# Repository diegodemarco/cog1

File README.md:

# cog1

## What is cog1?
cog1 is an open-source industrial IoT gateway (hardware and software) built as a motherboard hosting an [Orange Pi Zero 3](http://www.orangepi.org/html/hardWare/computerAndMicrocontrollers/details/Orange-Pi-Zero-3.html) linux SBC (Wiki [here](http://www.orangepi.org/orangepiwiki/index.php/Orange_Pi_Zero_3)).
- The motherboard was designed using [KiCad](https://www.kicad.org/).
- Its software uses the [.net core framework](https://dotnet.microsoft.com/) (currently at version 8) to provide the services running in the hardware, as well as the back-end web services for the UI.
- It also hosts the user interface (console), which is written  in [Angular](https://angular.dev/), based on the [Core-UI admin template](https://coreui.io/product/free-angular-admin-template/).
- In essence, it's a fully self-contained IoT gateway capable of interfacing with sensors and actuators directly, designed to process data, make local decisions, and communicate with external cloud services if needed.

### Features

#### Hardware
The cog1 platform currently supports:
- Powered by any DC supply from 12 to 24 VDC.
- Four digital inputs (isolated, using two [ISO 1212](https://www.ti.com/lit/ds/symlink/iso1212.pdf) chips from TI).
- Four digital outputs (relays, varistor-protected).
- Four analog voltage inputs (0-10 V, non-isolated), protected up to 48 VDC. The ADC is an [ADC128D818](https://www.ti.com/lit/ds/symlink/adc128d818.pdf) chip from TI.
- Four analog current inputs (0-20 mA, non isolated), protected up to 100 mA. Uses the same [ADC128D818](https://www.ti.com/lit/ds/symlink/adc128d818.pdf) chip as the voltage inputs.
- One RS-485 port (tested from 9600 to 115200 bauds). Support for Modbus RTU is already built on top of this.
- Battery-backed RTC.
- A simple but extensible user interface with a small OLED display and a rotary encoder + pushbutton.
- All connectivity inherited from the Orange Pi Zero 3 SBC
  - 1 Gb Ethernet
  - 2.4 + 5.8 GHz WiFi
  - Bluetooth 5
  - A front USB port (USB 2.0)

#### Software

The current software is rather basic, but includes everything needed to fully test the hardware. Additionally, the software already has the correct "architecture", i.e. it is designed as a linux service file that can be started, stopped, etc., and communicates with the hardware through a low-level i/o library created with native code (plain old C).

The front-end (console) is written in Angular, based on the [Core-UI admin template](https://coreui.io/product/free-angular-admin-template/), and it communicates with the back-end via web-services, which are already integrated in such a way that creating new controllers/endpoints and consuming them from the front-end is really simple. 

The following features are already implemented:
- Internal variables are fully supported. These match the actual hardware of the cog1.
- External variables can be defined as well, based on Modbus registers.
- Both Modbus RTU and Modbus TCP are supported, allowing reading and writing the most common types of registers in a variety of data types.
- Variables can be defined to be "polled" automatically. For variables bound to Modbus registers, this means that the respective registers are polled via RTU or TCP as needed.
- Writeable variables can be controlled/modified from the dashboard.
- Writeable variables bound to Modbus registers also trigger the respective write operations through RTU or TCP, which can be done from the dashboard.

The plan is to continue developing the software so that it can:
- Provide data-extraction web services.
- Communicate with external cloud services via MQTT or any other protocol that could be relevant.
- Allow running javascript code using [Jint](https://github.com/sebastienros/jint) to make it possible to compute complex variables, do edge data-processing, etc.
- Update the console UI to allow further management of all avaible functionality, as it grows over time.

### Hardware
#### PCB

The PCB has been designed using KiCad. It contains everything needed, including a 3D render. All components can be hand-soldered, but a few (essentially the AOZ regulator, the ADC, and the digital input isolators) require a bit of skills, as they are SSOP components. 

All capacitors, resistors, etc. are 0805 or bigger, so they can be hand-soldered with little effort. The PCB contains all necessary headers to allow the Orange Pi Zero 3 to be plugged in, inverted.

All components can be found in the usual marketplaces (DigiKey, Mouser, etc.). I strongly advice not using unreliable (i.e. unrealistically cheap) sources for the components, especially the chips, as there is a large market of fake chips that either don't work, or even worse, work erratically.

#### Enclosure
The enclosure for the cog1 is a rather standard extruded-aluminum case, which can be found online for a few bucks. However, as a 3D printing enthusiast, I ended up designing and printing everything necessary to complete the enclosure:
- Front cover
- Back cover
- Knob

All designs, done in SolidWorks, are included in this project. I have printed everything with an Elegoo Mars 3 Pro (resin), and expect that all parts would print well on any resin 3D printer. I have not tried to print this on a filament printer, as I believe the quality would not be good enough. When printed in resin, all parts really look production-grade if the proper resin is used.

### Software
#### Main back-end code
The main code of the cog1 platform is a .net core application that contains all the necessary components (web services and general logic) to keep the cog1 working. The current version is relatively basic, and only contains those features needed to test the hardware. A web service is in place to provide basic status of the cog1, which is currently used to test the overall reliability of the hardware. All hardware functions have been tested with this software.

This is by far the area that needs the most effort, so that the cog1 can be turned into a fully-functional gateway.

#### Native back-end code
There are a few small portions of the software written in plan old C, and compiled directly in the SBC:
- A low-level i/o library that deals with digital and analog i/o, display, etc.
- A small "logo" application (configured as a service that starts early in the Linux boot process) to display the cog1 logo while the cog1 is booting.

Everything else is c#, so there's no low-level really in the c# code. 

#### Front-end code
The front-end (console) is written in Angular, based on the [Core-UI admin template](https://coreui.io/product/free-angular-admin-template/), and it communicates with the back-end via web-services, which are already integrated in such a way that creating new controllers/endpoints and consuming them from the front-end is really simple. While the functionality is relatively limited at the moment, the front-end contains all the necessary building-blocks to be extended easily:
- It communicates with the back-end via web-services, with proxies created using [swagger-typescript-api](https://github.com/acacode/swagger-typescript-api). This makes it very simple to create new controllers and endpoints in the back-end andthen use them in the front-end with full type-checking and code insight.
- It handles authentication with the back-end.
- It fully supports loading literals (in the language of the user) from the back-end, before the application starts.

## Getting started
### Building the hardware
The KiCad project included in the pcb folder contains everything needed to manufacture the pcb. For all prototypes, the pcb was ordered to PCBWay, and then all components were soldered manually. When soldering, I strongly advise mounting the switching power supply first, veryfying the 5V are steady and noiseless, and then mount everything else. This is to prevent blowing up anything if the switching power supply was not mounted correctly.

### Installing the software
I'll write a tutorial for this ASAP, but it's pretty straightforward.

## Current status
### What's done
### What's missing

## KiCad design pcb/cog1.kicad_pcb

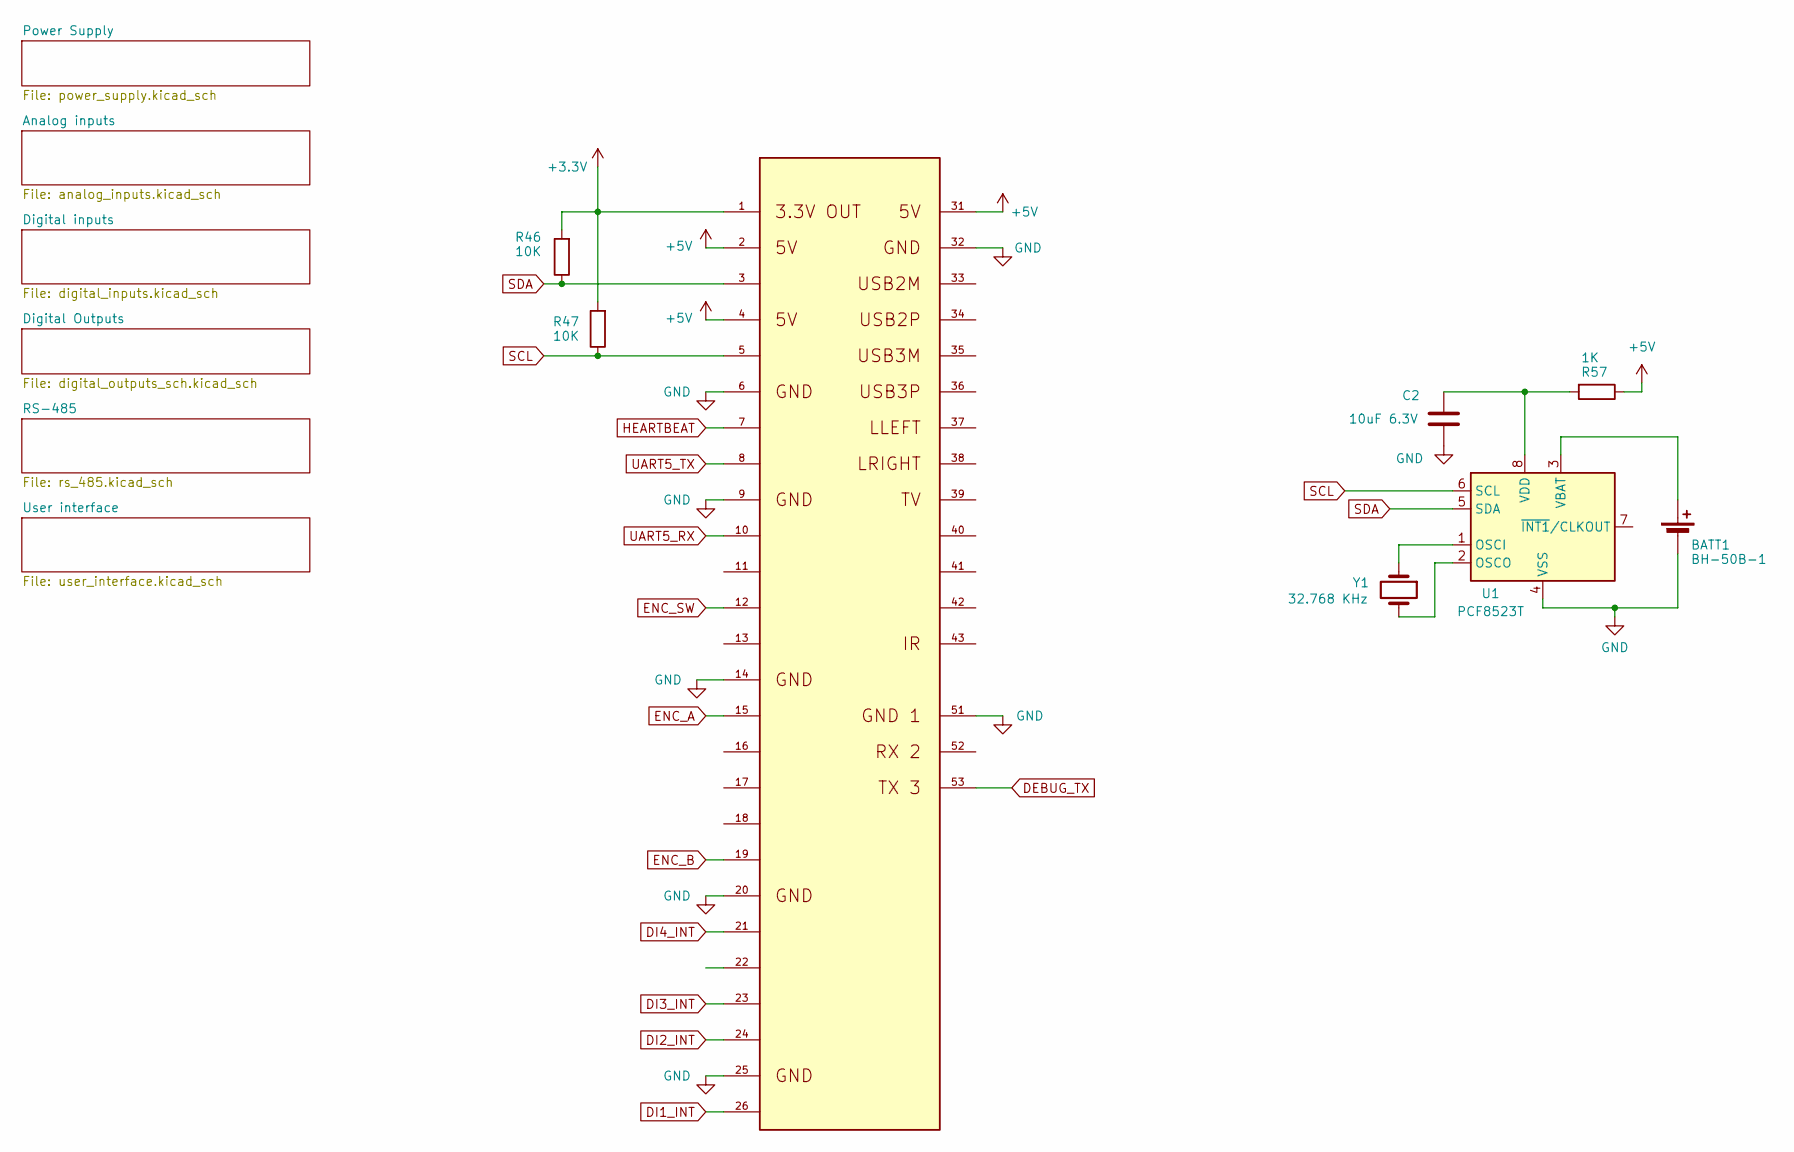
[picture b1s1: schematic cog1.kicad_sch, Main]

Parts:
BATT1: BH-50B-1
C2: 10uF 6.3V; C_0805_2012Metric
R46, R47: 10K; R_0805_2012Metric
R57: 1K; R_0805_2012Metric
U1: PCF8523T; SOIC-8_3.9x4.9mm_P1.27mm
U$1: OPI-ZERO-3
Y1: 32.768 KHz; Crystal_C26-LF_D2.1mm_L6.5mm_Vertical

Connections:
+3.3V: R46.2, R47.2, U$1.1; also elsewhere on the board
+5V: R57.1, U$1.2, U$1.4, U$1.31; also elsewhere on the board
DEBUG_TX: U$1.53; also elsewhere on the board
DI1_INT: U$1.26; also elsewhere on the board
DI2_INT: U$1.24; also elsewhere on the board
DI3_INT: U$1.23; also elsewhere on the board
DI4_INT: U$1.21; also elsewhere on the board
ENC_A: U$1.15; also elsewhere on the board
ENC_B: U$1.19; also elsewhere on the board
ENC_SW: U$1.12; also elsewhere on the board
GND: BATT1.2 (-), C2.1, U1.4 (VSS), U$1.6, U$1.9, U$1.14, U$1.20, U$1.25, U$1.32, U$1.51; also elsewhere on the board
HEARTBEAT: U$1.7; also elsewhere on the board
unnamed: BATT1.1 (+), U1.3 (VBAT)
unnamed: U1.1 (OSCI), Y1.1
unnamed: U1.2 (OSCO), Y1.2
unnamed: C2.2, R57.2, U1.8 (VDD)
SCL: R47.1, U1.6 (SCL), U$1.5; also elsewhere on the board
SDA: R46.1, U1.5 (SDA), U$1.3; also elsewhere on the board
UART5_RX: U$1.10; also elsewhere on the board
UART5_TX: U$1.8; also elsewhere on the board

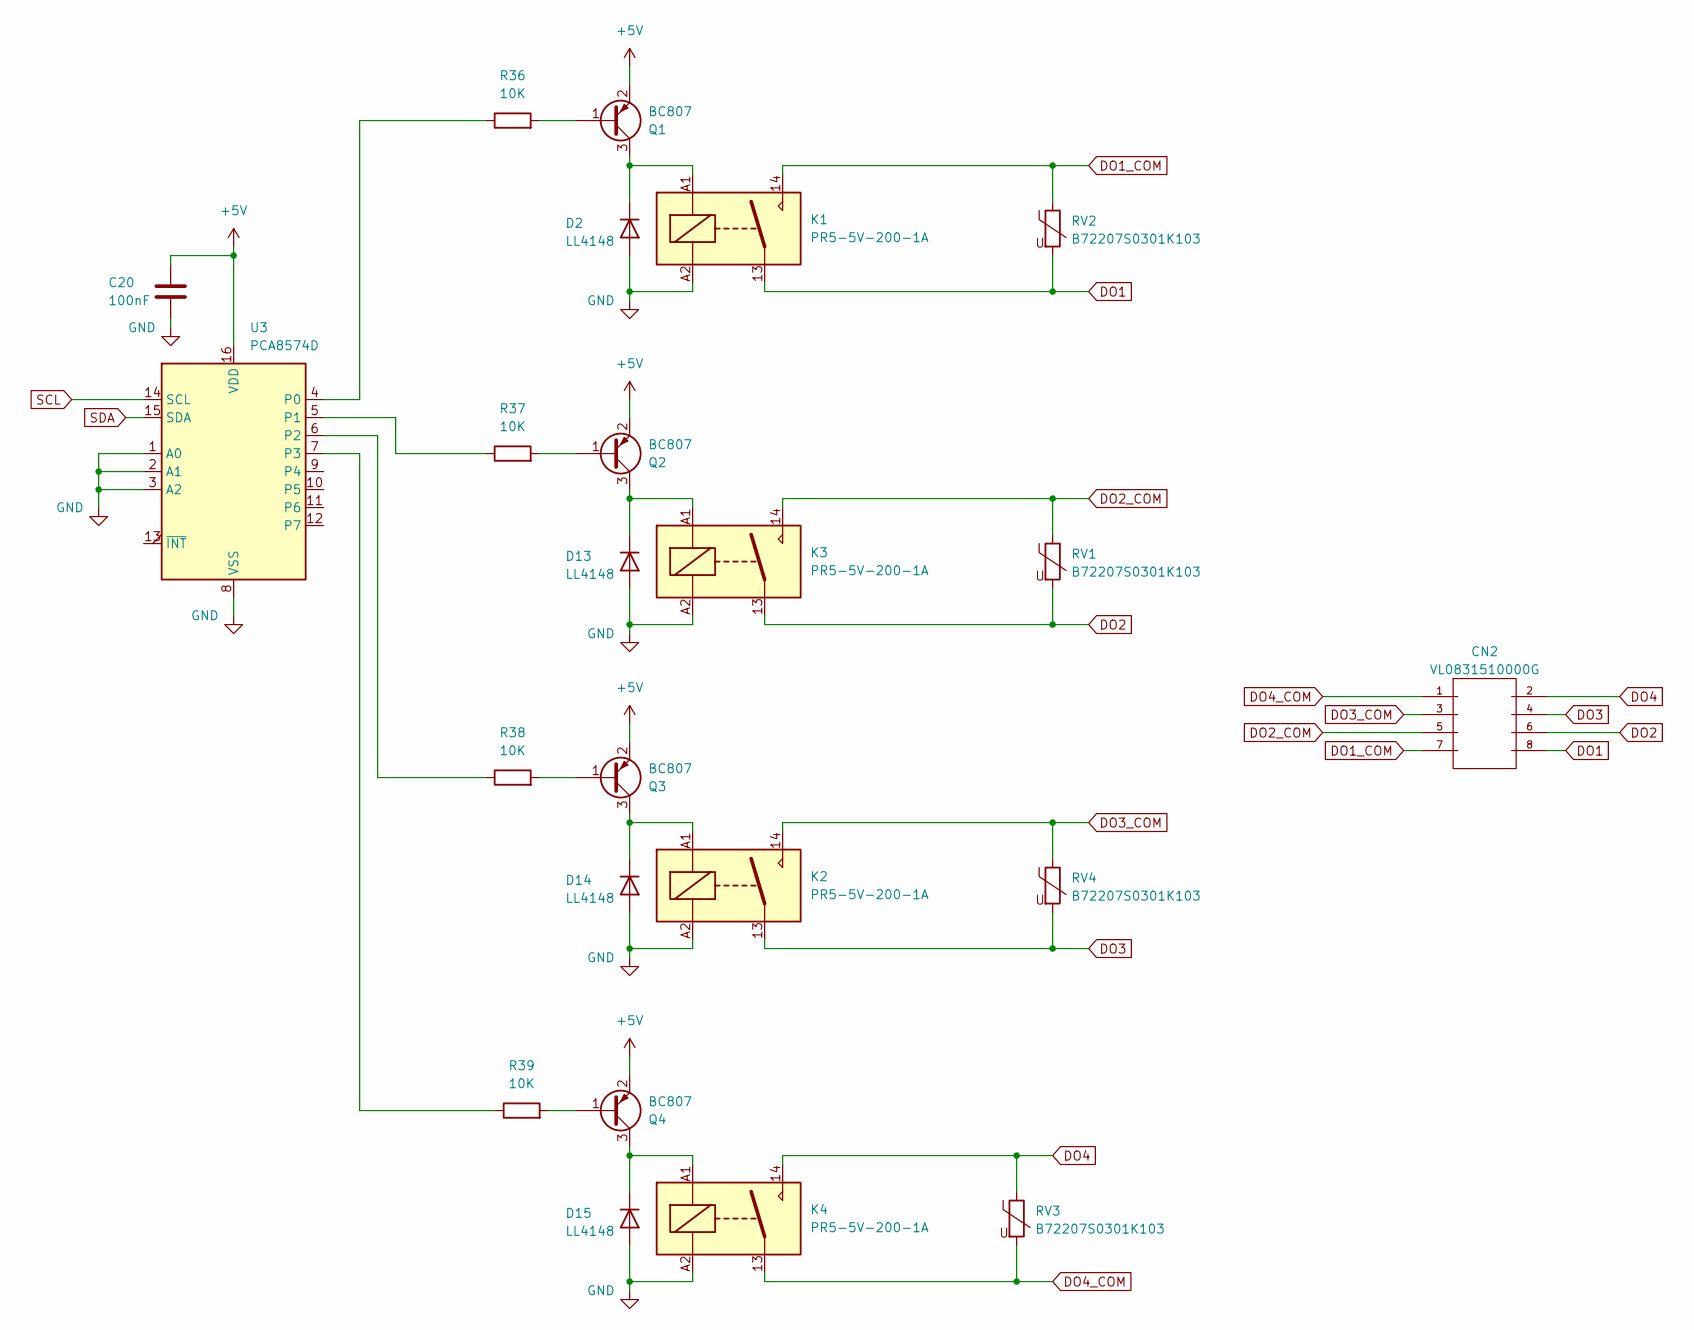
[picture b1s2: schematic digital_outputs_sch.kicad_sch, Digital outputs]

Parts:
C20: 100nF; C_0805_2012Metric
CN2: VL0831510000G
D2, D13, D14, D15: LL4148; D_MiniMELF
K1, K2, K3, K4: PR5-5V-200-1A
Q1, Q2, Q3, Q4: BC807; SOT-23
R36, R37, R38, R39: 10K; R_0805_2012Metric
RV1, RV2, RV3, RV4: B72207S0301K103; RV_Disc_D7mm_W4.5mm_P5mm
U3: PCA8574D; SOIC-16W_7.5x10.3mm_P1.27mm

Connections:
+5V: C20.1, Q1.2 (E), Q2.2 (E), Q3.2 (E), Q4.2 (E), U3.16 (VDD); also elsewhere on the board
DO1: CN2.8, K1.13, RV2.2
DO1_COM: CN2.7, K1.14, RV2.1
DO2: CN2.6, K3.13, RV1.2
DO2_COM: CN2.5, K3.14, RV1.1
DO3: CN2.4, K2.13, RV4.2
DO3_COM: CN2.3, K2.14, RV4.1
DO4: CN2.2, K4.14, RV3.1
DO4_COM: CN2.1, K4.13, RV3.2
GND: C20.2, D2.2 (A), D13.2 (A), D14.2 (A), D15.2 (A), K1.A2, K2.A2, K3.A2, K4.A2, U3.1 (A0), U3.2 (A1), U3.3 (A2), U3.8 (VSS); also elsewhere on the board
unnamed: D2.1 (K), K1.A1, Q1.3 (C)
unnamed: D13.1 (K), K3.A1, Q2.3 (C)
unnamed: D14.1 (K), K2.A1, Q3.3 (C)
unnamed: D15.1 (K), K4.A1, Q4.3 (C)
unnamed: Q1.1 (B), R36.2
unnamed: Q2.1 (B), R37.2
unnamed: Q3.1 (B), R38.2
unnamed: Q4.1 (B), R39.2
unnamed: R36.1, U3.4 (P0)
unnamed: R37.1, U3.5 (P1)
unnamed: R38.1, U3.6 (P2)
unnamed: R39.1, U3.7 (P3)
SCL: U3.14 (SCL); also elsewhere on the board
SDA: U3.15 (SDA); also elsewhere on the board

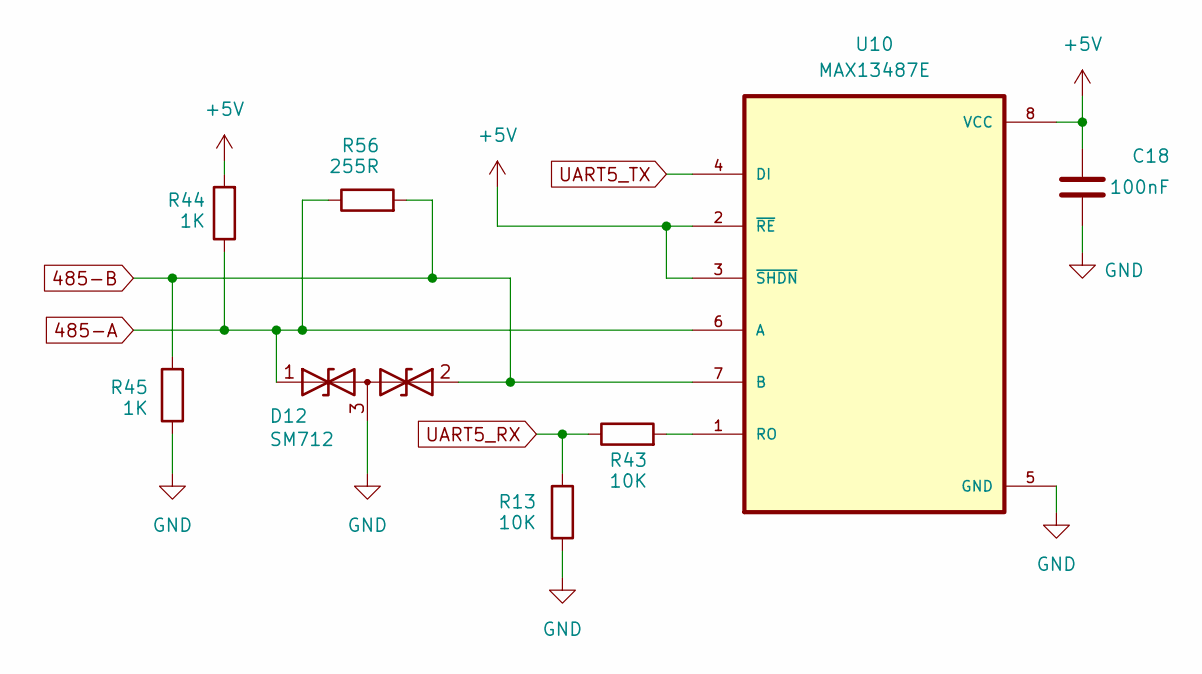
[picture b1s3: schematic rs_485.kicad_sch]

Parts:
C18: 100nF; C_0805_2012Metric
D12: SM712; SOT-23-3
R13, R43: 10K; R_0805_2012Metric
R44, R45: 1K; R_0805_2012Metric
R56: 255R; R_0805_2012Metric
U10: MAX13487E; SOIC-8_3.9x4.9mm_P1.27mm

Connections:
485-A: D12.1 (A1), R44.1, R56.1, U10.6 (A); also elsewhere on the board
485-B: D12.2 (A2), R45.2, R56.2, U10.7 (B); also elsewhere on the board
+5V: C18.2, R44.2, U10.2 (~RE), U10.3 (~SHDN), U10.8 (VCC); also elsewhere on the board
GND: C18.1, D12.3 (common), R13.2, R45.1, U10.5 (GND); also elsewhere on the board
unnamed: R43.2, U10.1 (RO)
UART5_RX: R13.1, R43.1; also elsewhere on the board
UART5_TX: U10.4 (DI); also elsewhere on the board

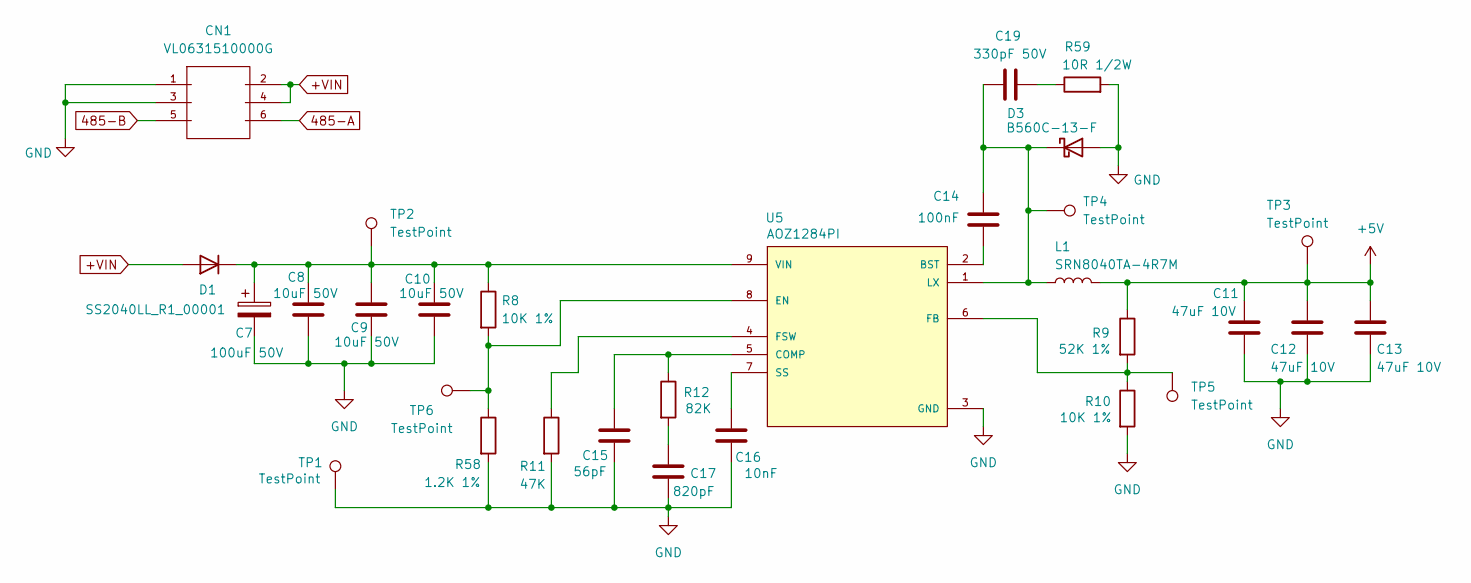
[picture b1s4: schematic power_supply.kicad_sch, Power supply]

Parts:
C7: 100uF 50V; CP_Elec_10x12.6
C8, C9, C10: 10uF 50V; C_1206_3216Metric_Pad1.33x1.80mm_HandSolder
C11, C12, C13: 47uF 10V; C_1206_3216Metric_Pad1.33x1.80mm_HandSolder
C14: 100nF; C_0805_2012Metric
C15: 56pF; C_0805_2012Metric
C16: 10nF; C_0805_2012Metric
C17: 820pF; C_0805_2012Metric
C19: 330pF 50V; C_0805_2012Metric
CN1: VL0631510000G
D1: SS2040LL_R1_00001; D_SOD-123F
D3: B560C-13-F; D_SMC
L1: SRN8040TA-4R7M; Bourns_SRN8040TA
R8, R10: 10K 1%; R_0805_2012Metric
R9: 52K 1%; R_0805_2012Metric
R11: 47K; R_0805_2012Metric
R12: 82K; R_0805_2012Metric
R58: 1.2K 1%; R_0805_2012Metric
R59: 10R 1/2W; R_1206_3216Metric_Pad1.30x1.75mm_HandSolder
TP1, TP2, TP3, TP4, TP5, TP6: TestPoint; TestPoint_Pad_D1.0mm
U5: AOZ1284PI

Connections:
485-A: CN1.6; also elsewhere on the board
485-B: CN1.5; also elsewhere on the board
+5V: C11.1, C12.1, C13.1, L1.2, R9.1, TP3.1; also elsewhere on the board
+VIN: CN1.2, CN1.4, D1.2 (A)
GND: C7.2, C8.2, C9.2, C10.2, C11.2, C12.2, C13.2, C15.1, C16.1, C17.1, CN1.1, CN1.3, D3.2 (A), R10.2, R11.2, R58.2, R59.2, TP1.1, U5.3 (GND); also elsewhere on the board
unnamed: C17.2, R12.2
unnamed: C19.1, R59.1
unnamed: C7.1, C8.1, C9.1, C10.1, D1.1 (K), R8.1, TP2.1, U5.9 (VIN)
unnamed: C14.2, C19.2, D3.1 (K), L1.1, TP4.1, U5.1 (LX)
unnamed: C14.1, U5.2 (BST)
unnamed: C15.2, R12.1, U5.5 (COMP)
unnamed: R8.2, R58.1, TP6.1, U5.8 (EN)
unnamed: R9.2, R10.1, TP5.1, U5.6 (FB)
unnamed: R11.1, U5.4 (FSW)
unnamed: C16.2, U5.7 (SS)

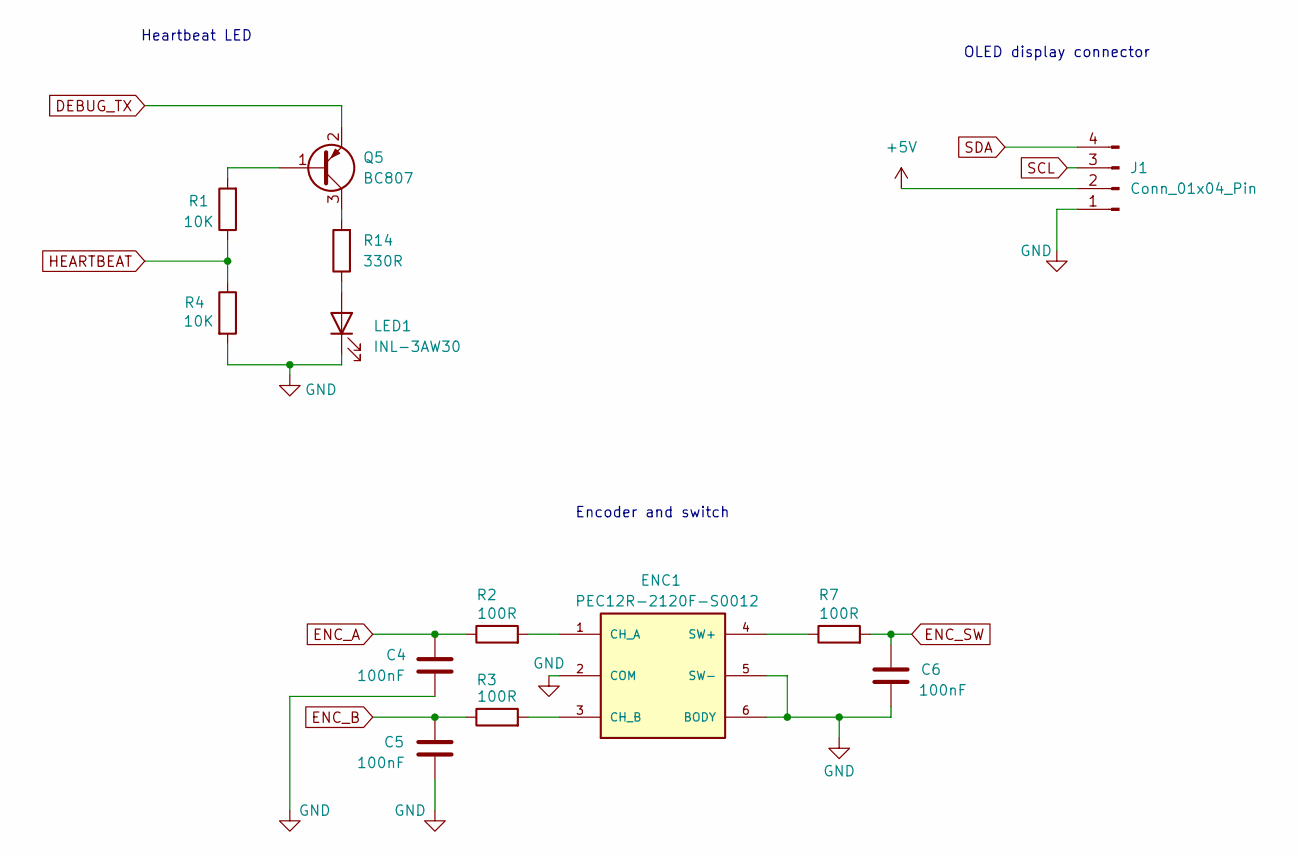
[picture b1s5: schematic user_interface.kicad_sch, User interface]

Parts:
C4, C5, C6: 100nF; C_0805_2012Metric
ENC1: PEC12R-2120F-S0012; BOURNS_PEC_HORZ_20
J1: Conn_01x04_Pin; PinHeader_1x04_P2.54mm_Vertical
LED1: INL-3AW30; LED_0805_2012Metric_Pad1.15x1.40mm_HandSolder
Q5: BC807; SOT-23
R1, R4: 10K; R_0805_2012Metric
R2, R3, R7: 100R; R_0805_2012Metric
R14: 330R; R_0805_2012Metric

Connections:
+5V: J1.2; also elsewhere on the board
DEBUG_TX: Q5.2 (E); also elsewhere on the board
ENC_A: C4.1, R2.1; also elsewhere on the board
ENC_B: C5.1, R3.1; also elsewhere on the board
ENC_SW: C6.1, R7.2; also elsewhere on the board
GND: C4.2, C5.2, C6.2, ENC1.2 (COM), ENC1.5 (SW-), ENC1.6 (BODY), J1.1, LED1.1 (K), R4.2; also elsewhere on the board
HEARTBEAT: R1.1, R4.1; also elsewhere on the board
unnamed: ENC1.1 (CH_A), R2.2
unnamed: ENC1.3 (CH_B), R3.2
unnamed: ENC1.4 (SW+), R7.1
unnamed: LED1.2 (A), R14.1
unnamed: Q5.1 (B), R1.2
unnamed: Q5.3 (C), R14.2
SCL: J1.3; also elsewhere on the board
SDA: J1.4; also elsewhere on the board

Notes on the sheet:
Encoder and switch
Heartbeat LED
OLED display connector

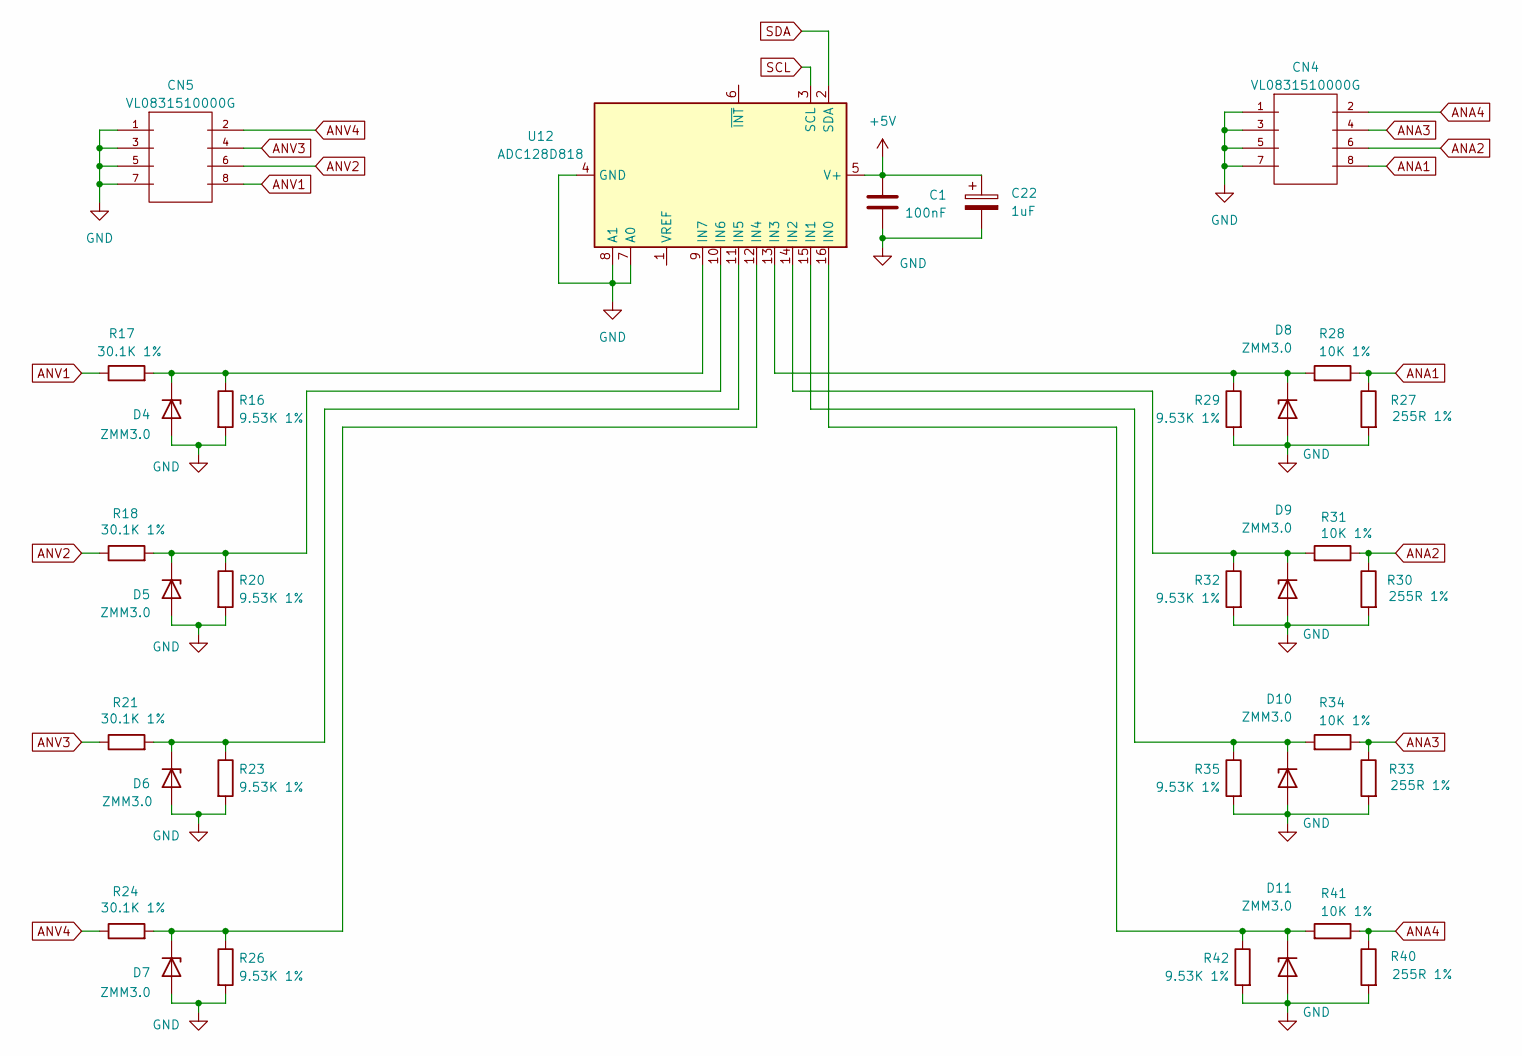
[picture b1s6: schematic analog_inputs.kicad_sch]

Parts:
C1: 100nF; C_0805_2012Metric
C22: 1uF; CP_EIA-3216-10_Kemet-I_Pad1.58x1.35mm_HandSolder
CN4, CN5: VL0831510000G
D4, D5, D6, D7, D8, D9, D10, D11: ZMM3.0; D_MiniMELF
R16, R20, R23, R26, R29, R32, R35, R42: 9.53K 1%; R_0805_2012Metric
R17, R18, R21, R24: 30.1K 1%; R_0805_2012Metric
R27, R30, R33, R40: 255R 1%; R_0805_2012Metric
R28, R31, R34, R41: 10K 1%; R_0805_2012Metric
U12: ADC128D818; TSSOP-16_4.4x5mm_P0.65mm

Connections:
+5V: C1.1, C22.1, U12.5 (V+); also elsewhere on the board
ANA1: CN4.8, R27.1, R28.1
ANA2: CN4.6, R30.1, R31.1
ANA3: CN4.4, R33.1, R34.1
ANA4: CN4.2, R40.1, R41.1
ANV1: CN5.8, R17.1
ANV2: CN5.6, R18.1
ANV3: CN5.4, R21.1
ANV4: CN5.2, R24.1
GND: C1.2, C22.2, CN4.1, CN4.3, CN4.5, CN4.7, CN5.1, CN5.3, CN5.5, CN5.7, D4.2 (A), D5.2 (A), D6.2 (A), D7.2 (A), D8.2 (A), D9.2 (A), D10.2 (A), D11.2 (A), R16.2, R20.2, R23.2, R26.2, R27.2, R29.2, R30.2, R32.2, R33.2, R35.2, R40.2, R42.2, U12.4 (GND), U12.7 (A0), U12.8 (A1); also elsewhere on the board
unnamed: D4.1 (K), R16.1, R17.2, U12.9 (IN7)
unnamed: D5.1 (K), R18.2, R20.1, U12.10 (IN6)
unnamed: D6.1 (K), R21.2, R23.1, U12.11 (IN5)
unnamed: D7.1 (K), R24.2, R26.1, U12.12 (IN4)
unnamed: D8.1 (K), R28.2, R29.1, U12.13 (IN3)
unnamed: D9.1 (K), R31.2, R32.1, U12.14 (IN2)
unnamed: D10.1 (K), R34.2, R35.1, U12.15 (IN1)
unnamed: D11.1 (K), R41.2, R42.1, U12.16 (IN0)
SCL: U12.3 (SCL); also elsewhere on the board
SDA: U12.2 (SDA); also elsewhere on the board

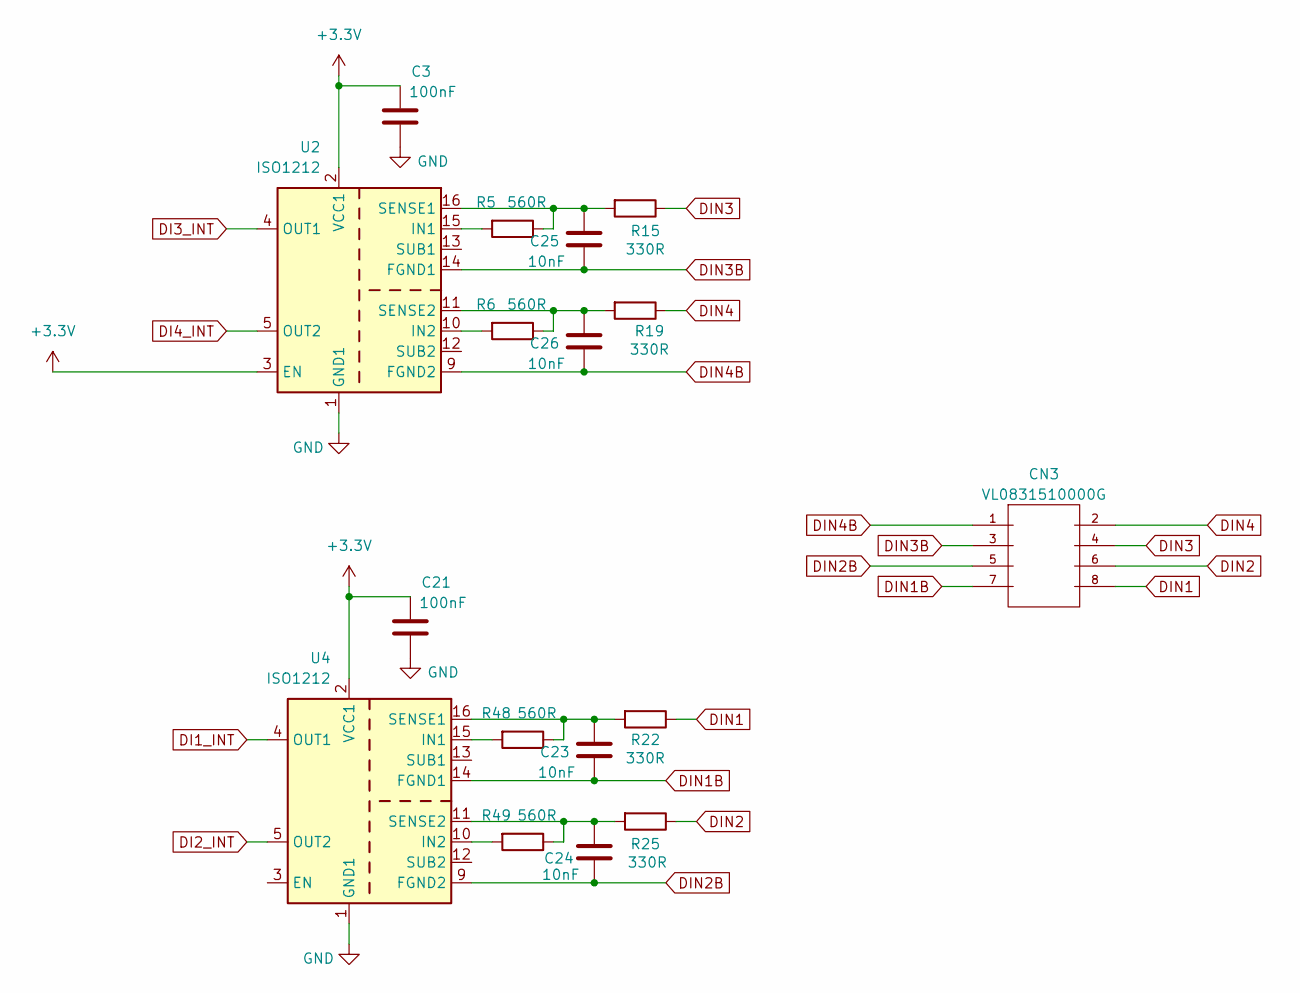
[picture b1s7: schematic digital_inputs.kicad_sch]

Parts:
C3, C21: 100nF; C_0805_2012Metric
C23, C24, C25, C26: 10nF; C_0805_2012Metric
CN3: VL0831510000G
R5, R6, R48, R49: 560R; R_0805_2012Metric
R15, R19, R22, R25: 330R; R_0805_2012Metric
U2, U4: ISO1212; SSOP-16_3.9x4.9mm_P0.635mm

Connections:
+3.3V: C3.1, C21.1, U2.2 (VCC1), U2.3 (EN), U4.2 (VCC1); also elsewhere on the board
DI1_INT: U4.4 (OUT1); also elsewhere on the board
DI2_INT: U4.5 (OUT2); also elsewhere on the board
DI3_INT: U2.4 (OUT1); also elsewhere on the board
DI4_INT: U2.5 (OUT2); also elsewhere on the board
DIN1: CN3.8, R22.1
DIN1B: C23.2, CN3.7, U4.14 (FGND1)
DIN2: CN3.6, R25.1
DIN2B: C24.2, CN3.5, U4.9 (FGND2)
DIN3: CN3.4, R15.1
DIN3B: C25.2, CN3.3, U2.14 (FGND1)
DIN4: CN3.2, R19.1
DIN4B: C26.2, CN3.1, U2.9 (FGND2)
GND: C3.2, C21.2, U2.1 (GND1), U2.8 (GND1), U4.1 (GND1), U4.8 (GND1); also elsewhere on the board
unnamed: R5.2, U2.15 (IN1)
unnamed: R6.2, U2.10 (IN2)
unnamed: C25.1, R5.1, R15.2, U2.16 (SENSE1)
unnamed: C26.1, R6.1, R19.2, U2.11 (SENSE2)
unnamed: R48.2, U4.15 (IN1)
unnamed: R49.2, U4.10 (IN2)
unnamed: C23.1, R22.2, R48.1, U4.16 (SENSE1)
unnamed: C24.1, R25.2, R49.1, U4.11 (SENSE2)

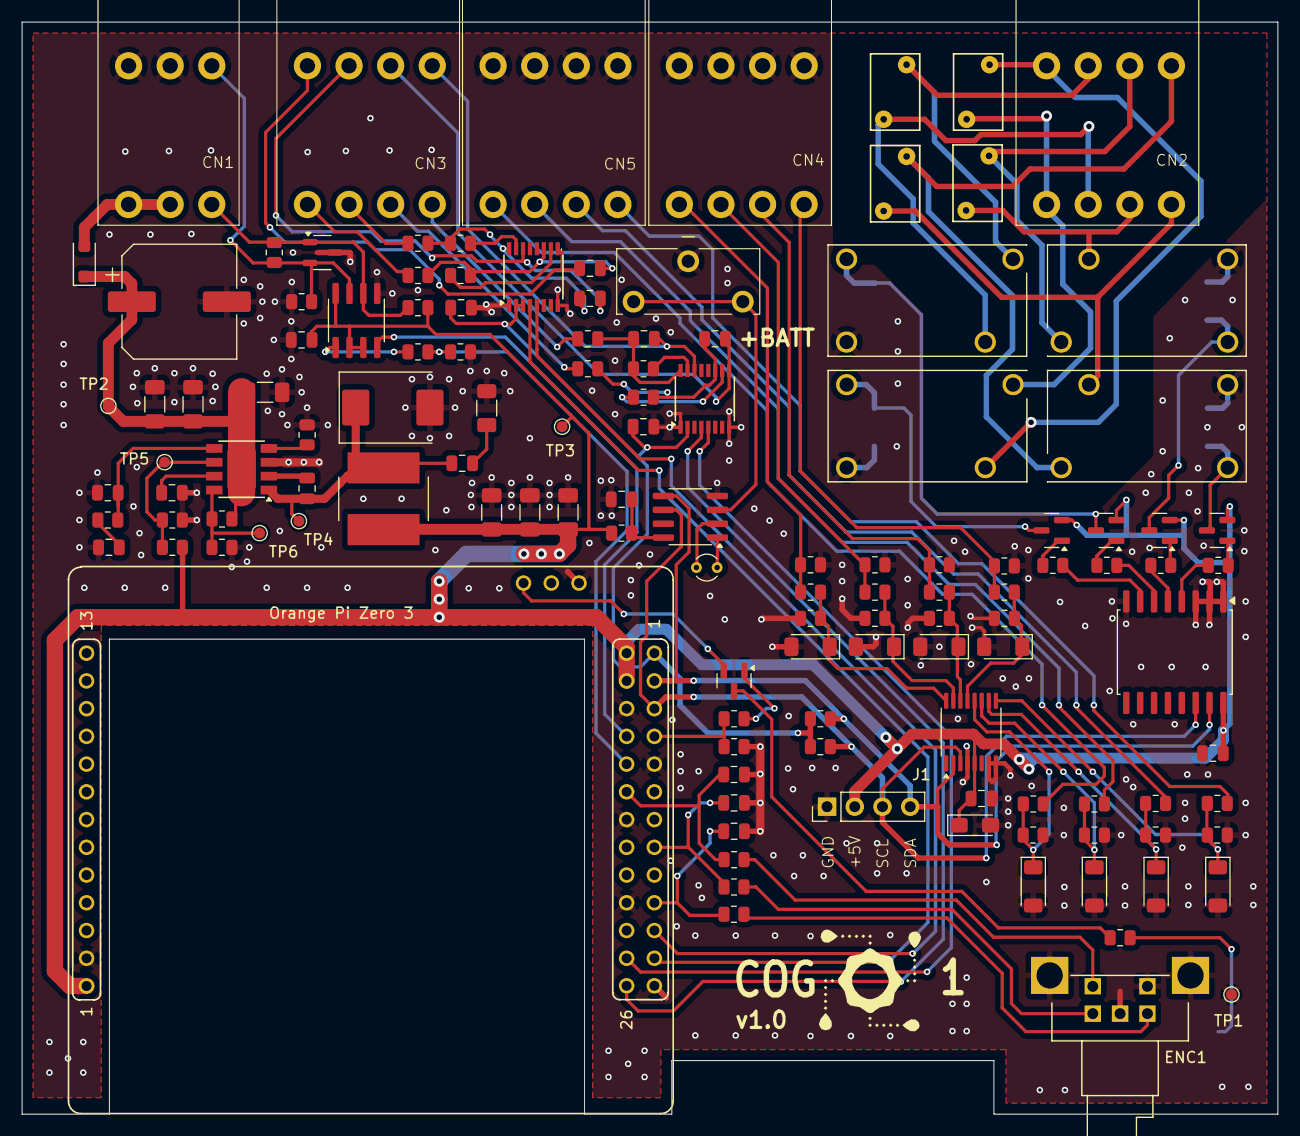
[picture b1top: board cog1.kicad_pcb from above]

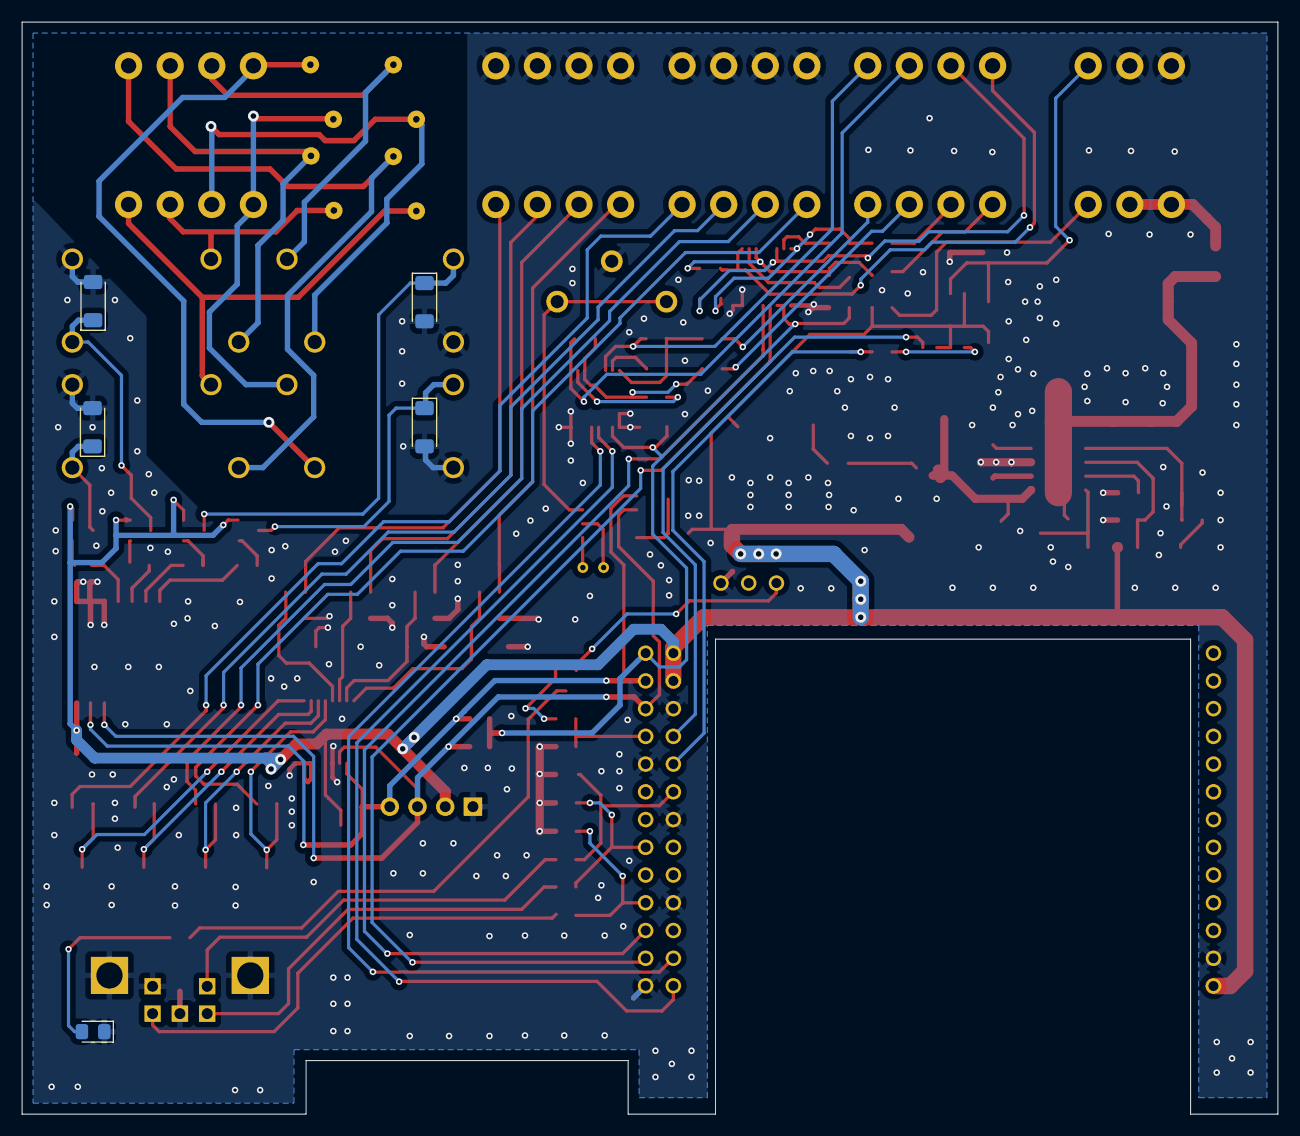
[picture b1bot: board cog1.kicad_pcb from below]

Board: 2 copper layers, 115.0 x 100.0 mm, 132 parts (5 on the bottom side), 92 nets.

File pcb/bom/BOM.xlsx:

Designator | Footprint | Quantity | Designation
R58 | R_0805_2012Metric | 1 | 1.2K 1%
C21,C4,C20,C5,C14,C3,C1,C18,C6 | C_0805_2012Metric | 9 | 100nF
R7,R3,R2 | R_0805_2012Metric | 3 | 100R
C7 | CP_Elec_10x12.6 | 1 | 100uF 50V
R43,R46,R8,R47,R1,R4,R13 | R_0805_2012Metric | 7 | 10K
R41,R31,R28,R10,R34 | R_0805_2012Metric | 5 | 10K 1%
C16 | C_0805_2012Metric | 1 | 10nF
R59 | R_0815_2038Metric_Pad1.20x4.05mm_HandSolder | 1 | 10R 1/2W
C10,C9,C8 | C_1206_3216Metric_Pad1.33x1.80mm_HandSolder | 3 | 10uF 50V
C2 | C_0805_2012Metric | 1 | 10uF 6.3V
R57,R39,R37,R44,R36,R45,R38 | R_0805_2012Metric | 7 | 1K
C22 | CP_EIA-3216-10_Kemet-I_Pad1.58x1.35mm_HandSolder | 1 | 1uF
R56 | R_0805_2012Metric | 1 | 255R
R33,R27,R30,R40 | R_0805_2012Metric | 4 | 255R 1%
R21,R18,R24,R17 | R_0805_2012Metric | 4 | 30.1K 1%
Y1 | Crystal_C26-LF_D2.1mm_L6.5mm_Vertical | 1 | 32.768 KHz
C19 | C_0805_2012Metric | 1 | 330pF 50V
R14 | R_0805_2012Metric | 1 | 330R
R11 | R_0805_2012Metric | 1 | 47K
C11,C13,C12 | C_1206_3216Metric_Pad1.33x1.80mm_HandSolder | 3 | 47uF 10V
R9 | R_0805_2012Metric | 1 | 52K 1%
R49,R48,R5,R6 | R_0805_2012Metric | 4 | 560R
C15 | C_0805_2012Metric | 1 | 56pF
C17 | C_0805_2012Metric | 1 | 820pF
R12 | R_0805_2012Metric | 1 | 82K
R29,R32,R26,R23,R35,R16,R20,R42 | R_0805_2012Metric | 8 | 9.53K 1%
U12 | TSSOP-16_4.4x5mm_P0.65mm | 1 | ADC128D818
U5 | Diodes_SO-8EP | 1 | AOZ1284PI
D3 | D_SMC | 1 | B560C-13-F
RV1,RV2,RV3,RV4 | RV_Disc_D7mm_W4.5mm_P5mm | 4 | B72207S0301K103
Q2,Q3,Q4,Q1,Q5 | SOT-23 | 5 | BC807
BATT1 | BH-50B-1 | 1 | BH-50B-1
J1 | PinHeader_1x04_P2.54mm_Vertical | 1 | Conn_01x04_Pin
LED1 | LED_0805_2012Metric_Pad1.15x1.40mm_HandSolder | 1 | INL-3AW30
U2,U4 | SSOP-16_3.9x4.9mm_P0.635mm | 2 | ISO1212
D14,D2,D15,D13 | D_MiniMELF | 4 | LL4148
U10 | SOIC-8_3.9x4.9mm_P1.27mm | 1 | MAX13487E
D11,D7,D9,D8,D4,D10,D6,D5 | D_SOD-123 | 8 | MMSZ4683
U$1 | OPI-ZERO-3 | 1 | OPI-ZERO-3
U3 | SOIC-16W_7.5x10.3mm_P1.27mm | 1 | PCA8574D
U1 | SOIC-8_3.9x4.9mm_P1.27mm | 1 | PCF8523T
ENC1 | BOURNS_PEC_HORZ_17 | 1 | PEC12R-2120F-S0012
K1,K3,K4,K2 | PR5-5V-200-1A | 4 | Relay_SPST-NO
D12 | SOT-23-3 | 1 | SM712
L1 | L_Bourns_SRN8040TA | 1 | SRN8040TA-4R7M
D1 | D_SOD-123F | 1 | SS2040LL_R1_00001
CN1 | VL0631510000G | 1 | VL0631510000G
CN3,CN4,CN2,CN5 | VL0831510000G | 4 | VL0831510000G
